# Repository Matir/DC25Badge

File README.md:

## Matir's DEF CON 25 Badge ##

This is an unofficial badge I made for DEF CON 25.  It's a blinding party-style
badge with 48 individually addressable RGB LEDs.  Off an adequate battery (a
medium LiPo) you can run all lights at max brightness, but that is *bright*.

This is intended as a one-time release for others to learn from and/or remix the
firmware.  I don't plan to take pull requests since it will be over and I'll be
on to another project by the release.  :)

### PCB ###

The PCB was designed using Kicad.  Source files are in the `dc25badge/`
directory.

### Compiling Firmware ###

To build the firmware, you'll need 3 things: this git repository, the Atmel
Software Framework (ASF), and an ARM compiler.  On Debian & Ubuntu, you'll want
to install the packages `gcc-arm-none-eabi` and `binutils-arm-none-eabi`.

`setup.sh` in the `src/` directory will get you the latest build of the ASF (at
least, it worked when this was prepared).  Running `make` will build the
firmware image.

To choose which patterns are available by pushing the mode button, edit the
array in `pattern.c`.

### Uploading Firmware ###

To upload a firmware image, you'll need to get into the bootloader.  To do this,
"double tap" the reset button, and the reset LED will stay solid green.  (If it
doesn't, you're not in the bootloader.)

You can then use `bossa` or just run `make upload` from the `src/` directory to
upload the current firmware build.

This is not an official Google product.

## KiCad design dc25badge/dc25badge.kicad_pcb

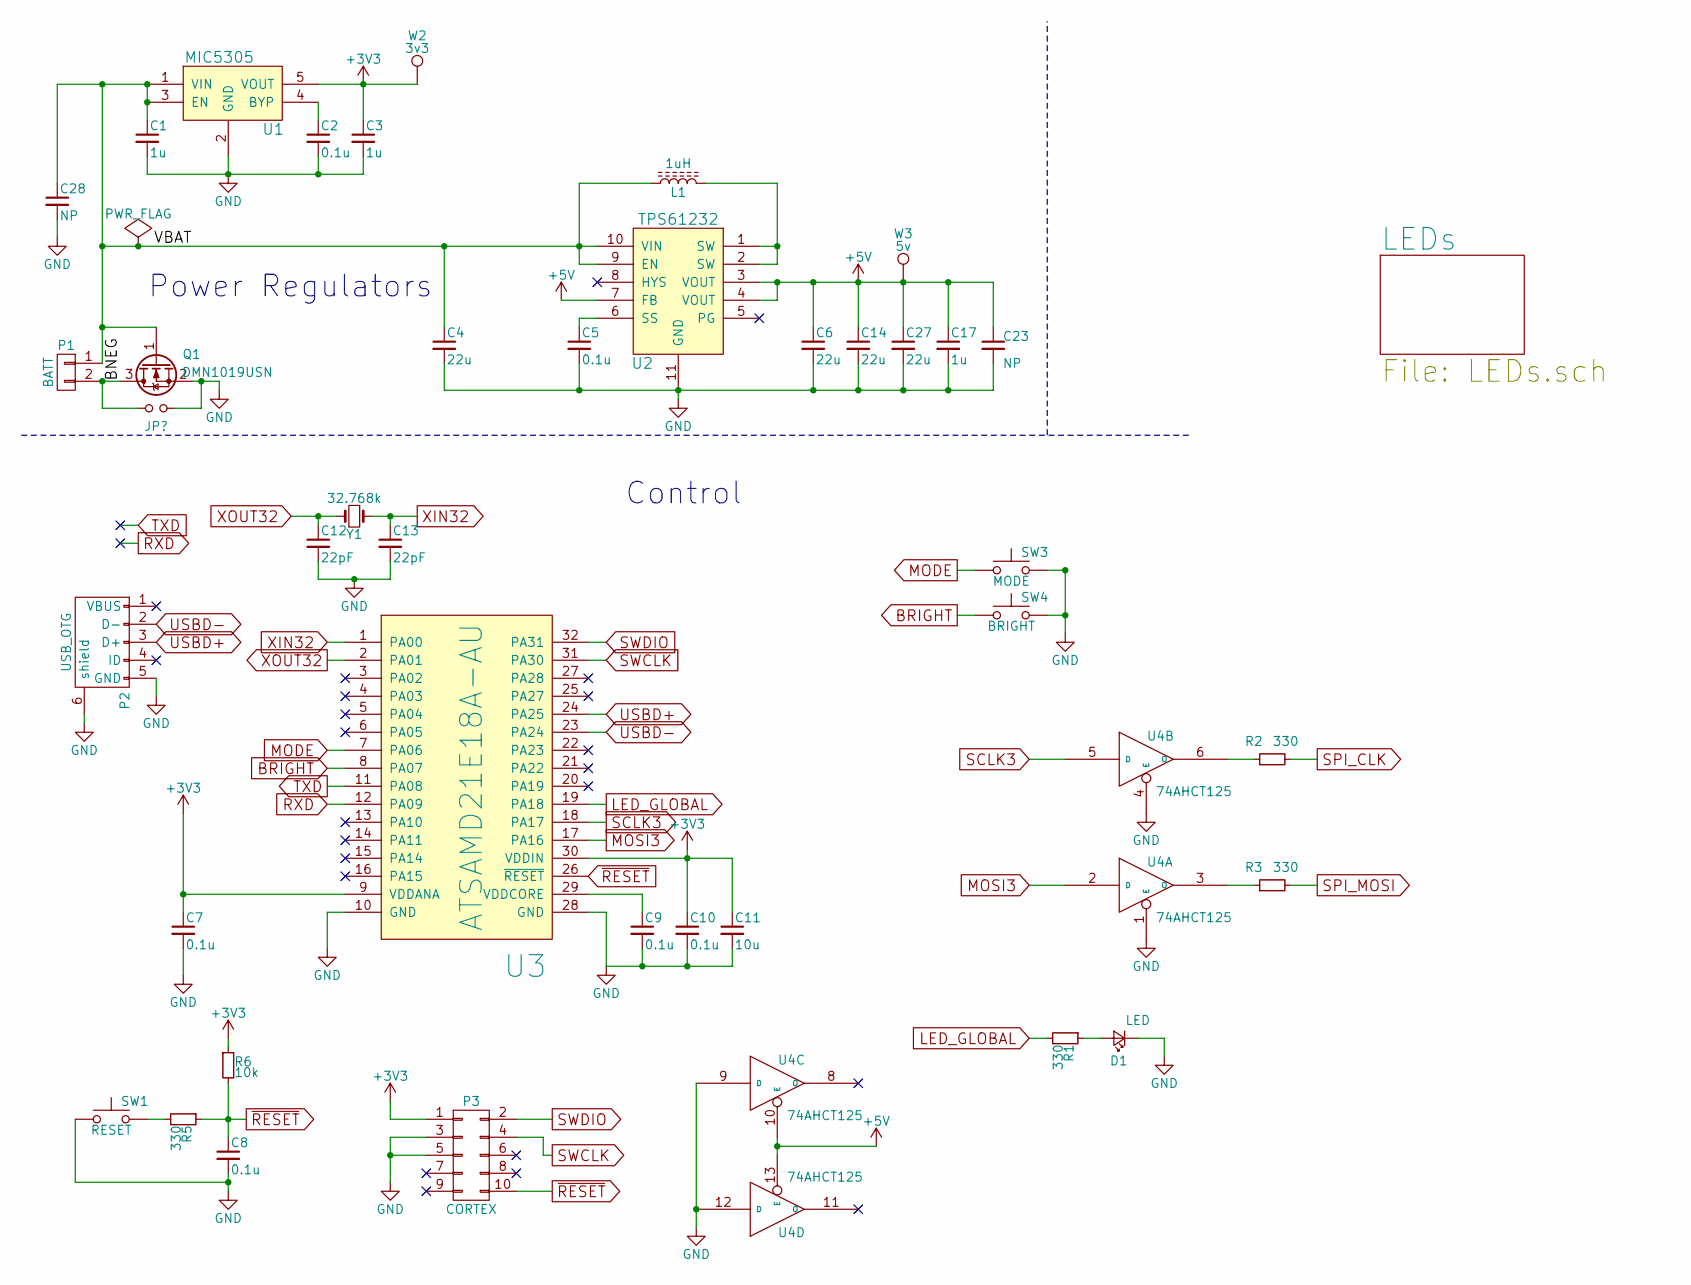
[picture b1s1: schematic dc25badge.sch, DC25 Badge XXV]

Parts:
C1, C3, C17: 1u; C_0805
C2, C5, C7, C8, C9, C10: 0.1u; C_0805
C4, C6, C14, C27: 22u; C_0805
C11: 10u; C_0805
C12, C13: 22pF; C_0603
C23, C28: NP; C_0805
D1: LED; LED_0805
L1: 1uH; Inductor_6.5x6
P1: BATT; JST_PH_S2B-PH-SM4-TB_02x2.00mm_Angled
P2: USB_OTG; Amphenol_10118192
P3: CORTEX; Pin_Header_Straight_2x05_Pitch1.27mm_SMD
Q1: DMN1019USN; SOT-23
R1, R2, R3, R5: 330; R_0805
R6: 10k; R_0805
SW1: RESET; SW_SPST_EVQP0
SW3: MODE; SW_SPST_EVQP0
SW4: BRIGHT; SW_SPST_EVQP0
U1: MIC5305; SOT-23-5
U2: TPS61232; PSON-10P
U3: ATSAMD21E18A-AU; TQFP-32_7x7mm_Pitch0.8mm
U4: 74AHCT125; SOIC-14_N
W2: 3v3; Measurement_Point_Round-SMD-Pad_Big
W3: 5v; Measurement_Point_Round-SMD-Pad_Big
Y1: 32.768k; Crystal_SMD_G8

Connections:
+3V3: C3.1, C7.1, C10.1, C11.1, P3.1, R6.1, U1.5 (VOUT), U3.9 (VDDANA), U3.30 (VDDIN), W2.1
+5V: C6.1, C14.1, C17.1, C23.1, C27.1, U2.3 (VOUT), U2.4 (VOUT), U2.7 (FB), U4.10 (E), U4.13 (E), U4.14 (+5V), W3.1; also elsewhere on the board
/BNEG: P1.2, Q1.3 (D); also elsewhere on the board
/VBAT: C1.1, C4.1, C28.1, L1.1, P1.1, Q1.1 (G), U1.1 (VIN), U1.3 (EN), U2.9 (EN), U2.10 (VIN)
BRIGHT: SW4.1, U3.8 (PA07)
GND: C1.2, C2.2, C3.2, C4.2, C5.2, C6.2, C7.2, C8.2, C9.2, C10.2, C11.2, C12.2, C13.2, C14.2, C17.2, C23.2, C27.2, C28.2, D1.1 (K), P2.5 (GND), P2.6 (shield), P3.3, P3.5, Q1.2 (S), SW1.1, SW3.2, SW4.2, U1.2 (GND), U2.11 (GND), U3.10 (GND), U3.28 (GND), U4.1 (E), U4.4 (E), U4.7 (GND), U4.9 (D), U4.12 (D); also elsewhere on the board
LED_GLOBAL: R1.2, U3.19 (PA18)
MODE: SW3.1, U3.7 (PA06)
MOSI3: U3.17 (PA16), U4.2 (D)
unnamed: C2.1, U1.4 (BYP)
unnamed: C5.1, U2.6 (SS)
unnamed: C9.1, U3.29 (VDDCORE)
unnamed: D1.2 (A), R1.1
unnamed: L1.2, U2.1 (SW), U2.2 (SW)
unnamed: R2.1, U4.6 (O)
unnamed: R3.1, U4.3 (O)
unnamed: R5.2, SW1.2
RXD: U3.12 (PA09)
SCLK3: U3.18 (PA17), U4.5 (D)
SPI_CLK: R2.2; also elsewhere on the board
SPI_MOSI: R3.2; also elsewhere on the board
SWCLK: P3.4, U3.31 (PA30)
SWDIO: P3.2, U3.32 (PA31)
TXD: U3.11 (PA08)
USBD+: P2.3 (D+), U3.24 (PA25)
USBD-: P2.2 (D-), U3.23 (PA24)
XIN32: C13.1, U3.1 (PA00), Y1.1
XOUT32: C12.1, U3.2 (PA01), Y1.2
~RESET: C8.1, P3.10, R5.1, R6.2, U3.26 (~RESET)

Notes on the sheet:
Power Regulators
Control

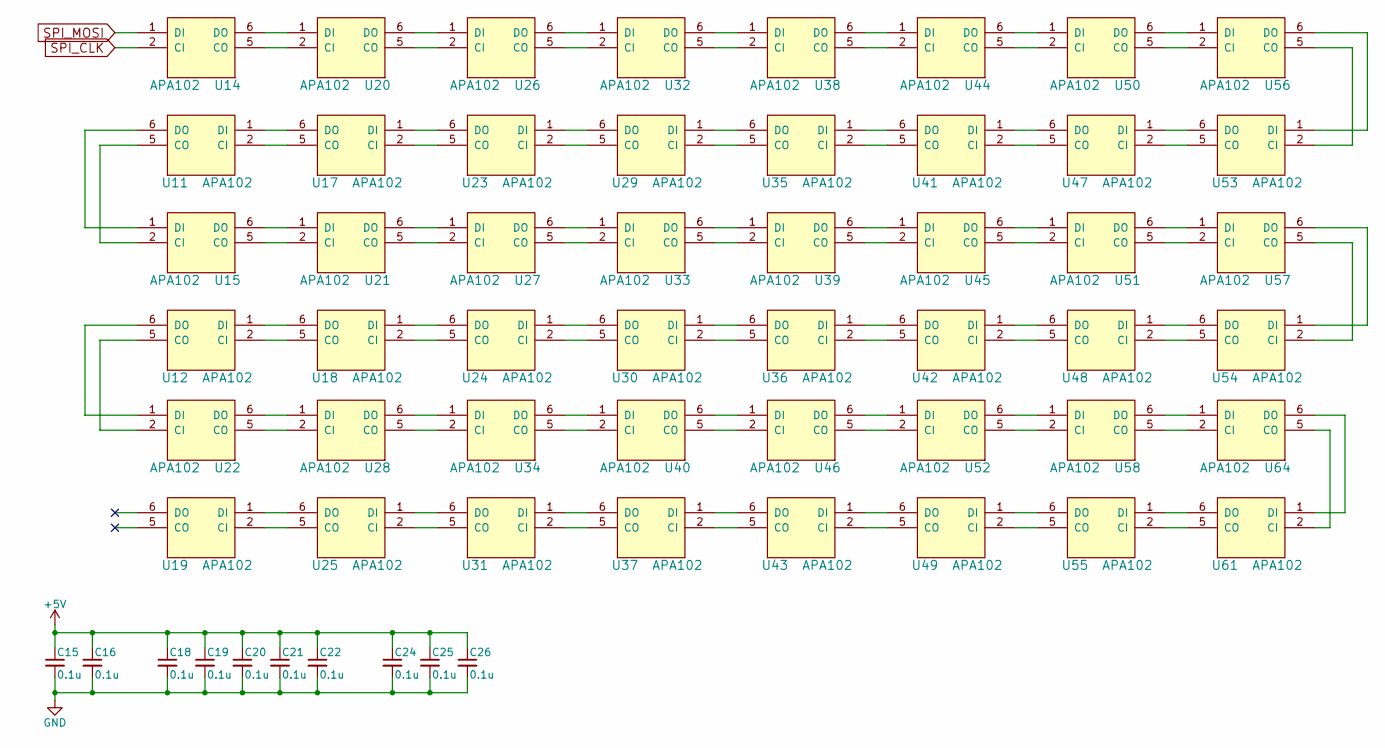
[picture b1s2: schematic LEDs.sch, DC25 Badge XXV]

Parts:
C15, C16, C18, C19, C20, C21, C22, C24, C25, C26: 0.1u; C_0805
U11, U12, U14, U15, U17, U18, U19, U20, U21, U22, U23, U24, U25, U26, U27, U28, U29, U30, U31, U32, U33, U34, U35, U36, U37, U38, U39, U40, U41, U42, U43, U44, U45, U46, U47, U48, U49, U50, U51, U52, U53, U54, U55, U56, U57, U58, U61, U64: APA102

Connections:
+5V: C15.1, C16.1, C18.1, C19.1, C20.1, C21.1, C22.1, C24.1, C25.1, C26.1, U11.4 (+5V), U12.4 (+5V), U14.4 (+5V), U15.4 (+5V), U17.4 (+5V), U18.4 (+5V), U19.4 (+5V), U20.4 (+5V), U21.4 (+5V), U22.4 (+5V), U23.4 (+5V), U24.4 (+5V), U25.4 (+5V), U26.4 (+5V), U27.4 (+5V), U28.4 (+5V), U29.4 (+5V), U30.4 (+5V), U31.4 (+5V), U32.4 (+5V), U33.4 (+5V), U34.4 (+5V), U35.4 (+5V), U36.4 (+5V), U37.4 (+5V), U38.4 (+5V), U39.4 (+5V), U40.4 (+5V), U41.4 (+5V), U42.4 (+5V), U43.4 (+5V), U44.4 (+5V), U45.4 (+5V), U46.4 (+5V), U47.4 (+5V), U48.4 (+5V), U49.4 (+5V), U50.4 (+5V), U51.4 (+5V), U52.4 (+5V), U53.4 (+5V), U54.4 (+5V), U55.4 (+5V), U56.4 (+5V), U57.4 (+5V), U58.4 (+5V), U61.4 (+5V), U64.4 (+5V); also elsewhere on the board
GND: C15.2, C16.2, C18.2, C19.2, C20.2, C21.2, C22.2, C24.2, C25.2, C26.2, U11.3 (GND), U12.3 (GND), U14.3 (GND), U15.3 (GND), U17.3 (GND), U18.3 (GND), U19.3 (GND), U20.3 (GND), U21.3 (GND), U22.3 (GND), U23.3 (GND), U24.3 (GND), U25.3 (GND), U26.3 (GND), U27.3 (GND), U28.3 (GND), U29.3 (GND), U30.3 (GND), U31.3 (GND), U32.3 (GND), U33.3 (GND), U34.3 (GND), U35.3 (GND), U36.3 (GND), U37.3 (GND), U38.3 (GND), U39.3 (GND), U40.3 (GND), U41.3 (GND), U42.3 (GND), U43.3 (GND), U44.3 (GND), U45.3 (GND), U46.3 (GND), U47.3 (GND), U48.3 (GND), U49.3 (GND), U50.3 (GND), U51.3 (GND), U52.3 (GND), U53.3 (GND), U54.3 (GND), U55.3 (GND), U56.3 (GND), U57.3 (GND), U58.3 (GND), U61.3 (GND), U64.3 (GND); also elsewhere on the board
unnamed: U11.1 (DI), U17.6 (DO)
unnamed: U11.2 (CI), U17.5 (CO)
unnamed: U11.5 (CO), U15.2 (CI)
unnamed: U11.6 (DO), U15.1 (DI)
unnamed: U12.1 (DI), U18.6 (DO)
unnamed: U12.2 (CI), U18.5 (CO)
unnamed: U12.5 (CO), U22.2 (CI)
unnamed: U12.6 (DO), U22.1 (DI)
unnamed: U14.5 (CO), U20.2 (CI)
unnamed: U14.6 (DO), U20.1 (DI)
unnamed: U15.5 (CO), U21.2 (CI)
unnamed: U15.6 (DO), U21.1 (DI)
unnamed: U17.1 (DI), U23.6 (DO)
unnamed: U17.2 (CI), U23.5 (CO)
unnamed: U18.1 (DI), U24.6 (DO)
unnamed: U18.2 (CI), U24.5 (CO)
unnamed: U19.1 (DI), U25.6 (DO)
unnamed: U19.2 (CI), U25.5 (CO)
unnamed: U20.5 (CO), U26.2 (CI)
unnamed: U20.6 (DO), U26.1 (DI)
unnamed: U21.5 (CO), U27.2 (CI)
unnamed: U21.6 (DO), U27.1 (DI)
unnamed: U22.5 (CO), U28.2 (CI)
unnamed: U22.6 (DO), U28.1 (DI)
unnamed: U23.1 (DI), U29.6 (DO)
unnamed: U23.2 (CI), U29.5 (CO)
unnamed: U24.1 (DI), U30.6 (DO)
unnamed: U24.2 (CI), U30.5 (CO)
unnamed: U25.1 (DI), U31.6 (DO)
unnamed: U25.2 (CI), U31.5 (CO)
unnamed: U26.5 (CO), U32.2 (CI)
unnamed: U26.6 (DO), U32.1 (DI)
unnamed: U27.5 (CO), U33.2 (CI)
unnamed: U27.6 (DO), U33.1 (DI)
unnamed: U28.5 (CO), U34.2 (CI)
unnamed: U28.6 (DO), U34.1 (DI)
unnamed: U29.1 (DI), U35.6 (DO)
unnamed: U29.2 (CI), U35.5 (CO)
unnamed: U30.1 (DI), U36.6 (DO)
unnamed: U30.2 (CI), U36.5 (CO)
unnamed: U31.1 (DI), U37.6 (DO)
unnamed: U31.2 (CI), U37.5 (CO)
unnamed: U32.5 (CO), U38.2 (CI)
unnamed: U32.6 (DO), U38.1 (DI)
unnamed: U33.5 (CO), U39.2 (CI)
unnamed: U33.6 (DO), U39.1 (DI)
unnamed: U34.5 (CO), U40.2 (CI)
unnamed: U34.6 (DO), U40.1 (DI)
unnamed: U35.1 (DI), U41.6 (DO)
unnamed: U35.2 (CI), U41.5 (CO)
unnamed: U36.1 (DI), U42.6 (DO)
unnamed: U36.2 (CI), U42.5 (CO)
unnamed: U37.1 (DI), U43.6 (DO)
unnamed: U37.2 (CI), U43.5 (CO)
unnamed: U38.5 (CO), U44.2 (CI)
unnamed: U38.6 (DO), U44.1 (DI)
unnamed: U39.5 (CO), U45.2 (CI)
unnamed: U39.6 (DO), U45.1 (DI)
unnamed: U40.5 (CO), U46.2 (CI)
unnamed: U40.6 (DO), U46.1 (DI)
unnamed: U41.1 (DI), U47.6 (DO)
unnamed: U41.2 (CI), U47.5 (CO)
unnamed: U42.1 (DI), U48.6 (DO)
unnamed: U42.2 (CI), U48.5 (CO)
unnamed: U43.1 (DI), U49.6 (DO)
unnamed: U43.2 (CI), U49.5 (CO)
unnamed: U44.5 (CO), U50.2 (CI)
unnamed: U44.6 (DO), U50.1 (DI)
unnamed: U45.5 (CO), U51.2 (CI)
unnamed: U45.6 (DO), U51.1 (DI)
unnamed: U46.5 (CO), U52.2 (CI)
unnamed: U46.6 (DO), U52.1 (DI)
unnamed: U47.1 (DI), U53.6 (DO)
unnamed: U47.2 (CI), U53.5 (CO)
unnamed: U48.1 (DI), U54.6 (DO)
unnamed: U48.2 (CI), U54.5 (CO)
unnamed: U49.1 (DI), U55.6 (DO)
unnamed: U49.2 (CI), U55.5 (CO)
unnamed: U50.5 (CO), U56.2 (CI)
unnamed: U50.6 (DO), U56.1 (DI)
unnamed: U51.5 (CO), U57.2 (CI)
unnamed: U51.6 (DO), U57.1 (DI)
unnamed: U52.5 (CO), U58.2 (CI)
unnamed: U52.6 (DO), U58.1 (DI)
unnamed: U53.1 (DI), U56.6 (DO)
unnamed: U53.2 (CI), U56.5 (CO)
unnamed: U54.1 (DI), U57.6 (DO)
unnamed: U54.2 (CI), U57.5 (CO)
unnamed: U55.1 (DI), U61.6 (DO)
unnamed: U55.2 (CI), U61.5 (CO)
unnamed: U58.5 (CO), U64.2 (CI)
unnamed: U58.6 (DO), U64.1 (DI)
unnamed: U61.1 (DI), U64.6 (DO)
unnamed: U61.2 (CI), U64.5 (CO)
SPI_CLK: U14.2 (CI); also elsewhere on the board
SPI_MOSI: U14.1 (DI); also elsewhere on the board

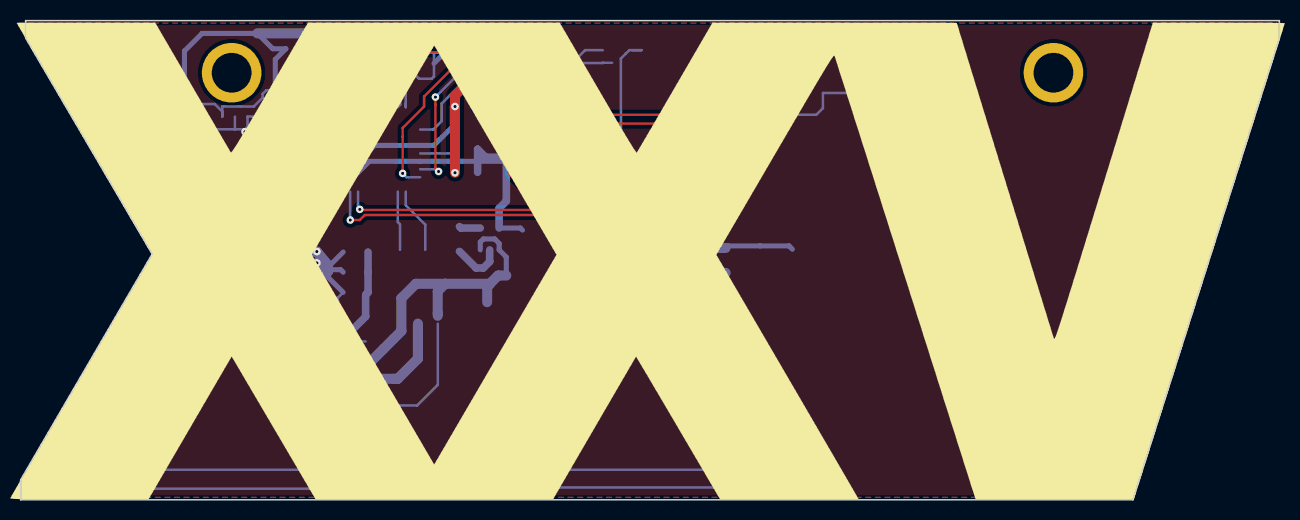
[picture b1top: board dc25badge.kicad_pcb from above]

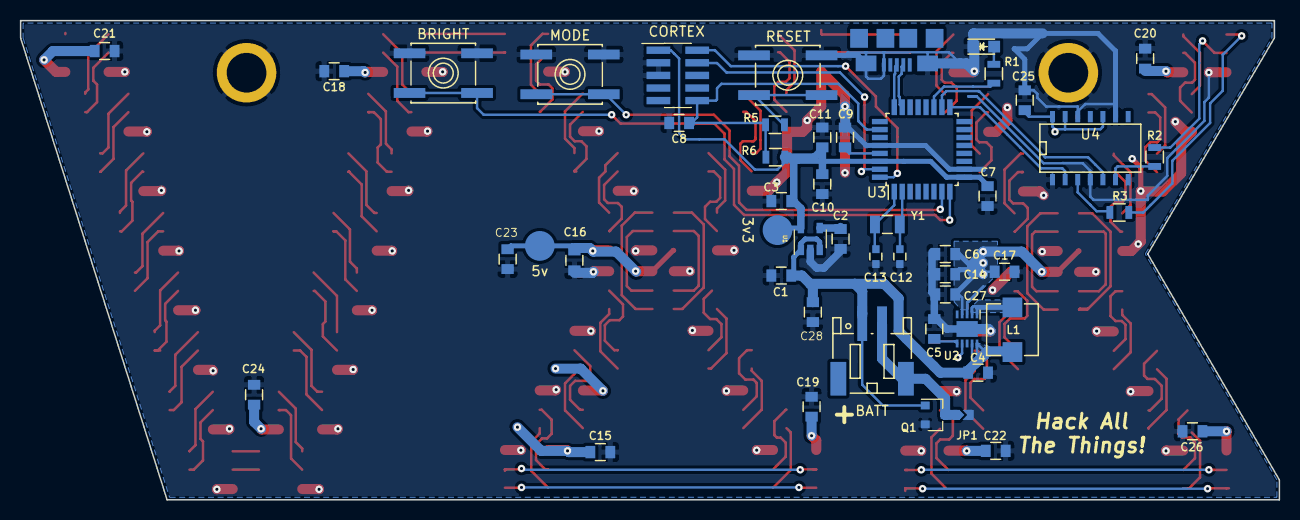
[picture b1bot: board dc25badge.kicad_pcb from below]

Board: 2 copper layers, 126.8 x 48.2 mm, 98 parts (50 on the bottom side), 121 nets.

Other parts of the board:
JP1: Jumper_NO_Small; JP_SOLDER

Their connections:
/BNEG: JP1.1; also elsewhere on the board
GND: JP1.2; also elsewhere on the board

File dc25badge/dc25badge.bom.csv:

Reference, Value, Footprint, Datasheet
"U1","MIC5305","TO_SOT_Packages_SMD:SOT-23-5",""
"P1","BATT","Connectors_JST:JST_PH_S2B-PH-SM4-TB_02x2.00mm_Angled",""
"C2","0.1u","Capacitors_SMD:C_0805",""
"C1","1u","Capacitors_SMD:C_0805",""
"C3","1u","Capacitors_SMD:C_0805",""
"U3","ATSAMD21E18A-AU","Housings_QFP:TQFP-32_7x7mm_Pitch0.8mm",""
"C7","0.1u","Capacitors_SMD:C_0805",""
"C9","0.1u","Capacitors_SMD:C_0805",""
"C10","0.1u","Capacitors_SMD:C_0805",""
"R6","10k","Resistors_SMD:R_0805",""
"C11","10u","Capacitors_SMD:C_0805",""
"C8","0.1u","Capacitors_SMD:C_0805",""
"R5","330","Resistors_SMD:R_0805",""
"SW1","RESET","Buttons_Switches_SMD:SW_SPST_EVQP0",""
"P3","CORTEX","Pin_Headers2:Pin_Header_Straight_2x05_Pitch1.27mm_SMD",""
"P2","USB_OTG","Badge_Parts:Amphenol_10118192",""
"U4","74AHCT125","SMD_Packages:SOIC-14_N",""
"W2","3v3","Measurement_Points:Measurement_Point_Round-SMD-Pad_Big",""
"W3","5v","Measurement_Points:Measurement_Point_Round-SMD-Pad_Big",""
"Y1","32.768k","Crystals:Crystal_SMD_G8",""
"C13","22pF","Capacitors_SMD:C_0603",""
"C12","22pF","Capacitors_SMD:C_0603",""
"SW3","MODE","Buttons_Switches_SMD:SW_SPST_EVQP0",""
"SW4","BRIGHT","Buttons_Switches_SMD:SW_SPST_EVQP0",""
"U2","TPS61232","Badge_Parts:PSON-10P",""
"C5","0.1u","Capacitors_SMD:C_0805",""
"L1","1uH","Badge_Parts:Inductor_6.5x6",""
"C4","22u","Capacitors_SMD:C_0805",""
"C6","22u","Capacitors_SMD:C_0805",""
"C14","22u","Capacitors_SMD:C_0805",""
"C27","22u","Capacitors_SMD:C_0805",""
"R1","330","Resistors_SMD:R_0805",""
"D1","LED","LEDs:LED_0805",""
"Q1","DMN1019USN","TO_SOT_Packages_SMD:SOT-23",""
"C17","1u","Capacitors_SMD:C_0805",""
"R2","330","Resistors_SMD:R_0805",""
"R3","330","Resistors_SMD:R_0805",""
"U38","APA102","Badge_Parts:APA102",""
"U44","APA102","Badge_Parts:APA102",""
"U50","APA102","Badge_Parts:APA102",""
"U56","APA102","Badge_Parts:APA102",""
"U14","APA102","Badge_Parts:APA102",""
"U20","APA102","Badge_Parts:APA102",""
"U26","APA102","Badge_Parts:APA102",""
"U32","APA102","Badge_Parts:APA102",""
"U29","APA102","Badge_Parts:APA102",""
"U23","APA102","Badge_Parts:APA102",""
"U17","APA102","Badge_Parts:APA102",""
"U11","APA102","Badge_Parts:APA102",""
"U53","APA102","Badge_Parts:APA102",""
"U47","APA102","Badge_Parts:APA102",""
"U41","APA102","Badge_Parts:APA102",""
"U35","APA102","Badge_Parts:APA102",""
"U39","APA102","Badge_Parts:APA102",""
"U45","APA102","Badge_Parts:APA102",""
"U51","APA102","Badge_Parts:APA102",""
"U57","APA102","Badge_Parts:APA102",""
"U15","APA102","Badge_Parts:APA102",""
"U21","APA102","Badge_Parts:APA102",""
"U27","APA102","Badge_Parts:APA102",""
"U33","APA102","Badge_Parts:APA102",""
"U30","APA102","Badge_Parts:APA102",""
"U24","APA102","Badge_Parts:APA102",""
"U18","APA102","Badge_Parts:APA102",""
"U12","APA102","Badge_Parts:APA102",""
"U54","APA102","Badge_Parts:APA102",""
"U48","APA102","Badge_Parts:APA102",""
"U42","APA102","Badge_Parts:APA102",""
"U36","APA102","Badge_Parts:APA102",""
"U40","APA102","Badge_Parts:APA102",""
"U46","APA102","Badge_Parts:APA102",""
"U52","APA102","Badge_Parts:APA102",""
"U58","APA102","Badge_Parts:APA102",""
"U64","APA102","Badge_Parts:APA102",""
"U22","APA102","Badge_Parts:APA102",""
"U28","APA102","Badge_Parts:APA102",""
"U34","APA102","Badge_Parts:APA102",""
"U31","APA102","Badge_Parts:APA102",""
"U25","APA102","Badge_Parts:APA102",""
"U19","APA102","Badge_Parts:APA102",""
"U61","APA102","Badge_Parts:APA102",""
"U55","APA102","Badge_Parts:APA102",""
"U49","APA102","Badge_Parts:APA102",""
"U43","APA102","Badge_Parts:APA102",""
"U37","APA102","Badge_Parts:APA102",""
"C15","0.1u","Capacitors_SMD:C_0805",""
"C16","0.1u","Capacitors_SMD:C_0805",""
"C18","0.1u","Capacitors_SMD:C_0805",""
"C19","0.1u","Capacitors_SMD:C_0805",""
"C20","0.1u","Capacitors_SMD:C_0805",""
"C21","0.1u","Capacitors_SMD:C_0805",""
"C22","0.1u","Capacitors_SMD:C_0805",""
"C24","0.1u","Capacitors_SMD:C_0805",""
"C25","0.1u","Capacitors_SMD:C_0805",""
"C26","0.1u","Capacitors_SMD:C_0805",""

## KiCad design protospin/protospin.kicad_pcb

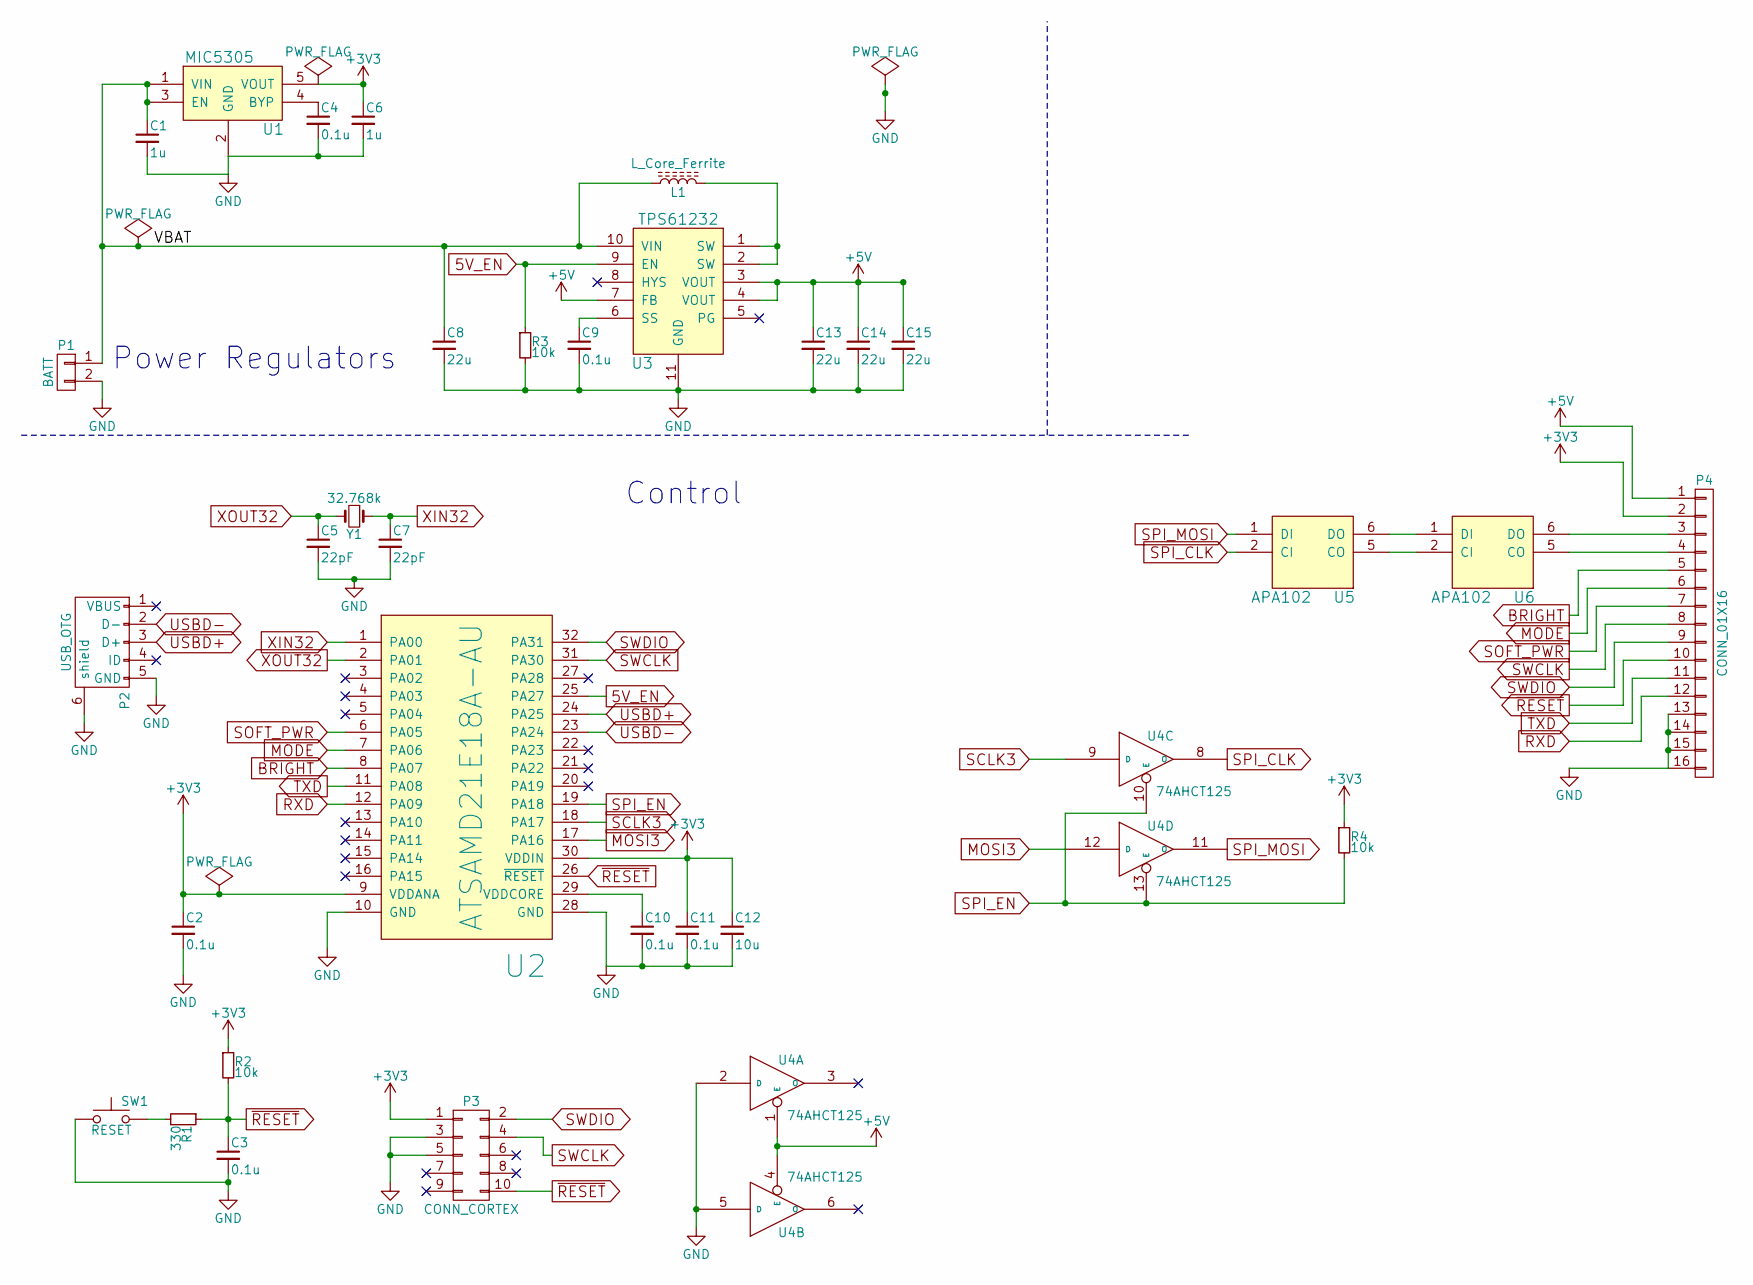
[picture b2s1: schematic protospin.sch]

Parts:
C1, C6: 1u; C_0805_HandSoldering
C2, C3, C4, C9, C10, C11: 0.1u; C_0805_HandSoldering
C5, C7: 22pF; C_0805_HandSoldering
C8, C13, C14, C15: 22u; C_0805_HandSoldering
C12: 10u; C_0805_HandSoldering
L1: L_Core_Ferrite; Inductor_6.5x6
P1: BATT; JST_PH_S2B-PH-SM4-TB_02x2.00mm_Angled
P2: USB_OTG; Amphenol_10118192
P3: CONN_CORTEX; Pin_Header_Straight_2x05_Pitch1.27mm_SMD
P4: CONN_01X16; Pin_Header_Straight_1x16_Pitch2.54mm_SMD_Pin1Right
R1: 330; R_0805_HandSoldering
R2, R3, R4: 10k; R_0805_HandSoldering
SW1: RESET; SW_SPST_EVQP0
U1: MIC5305; SOT-23-5
U2: ATSAMD21E18A-AU; TQFP-32_7x7mm_Pitch0.8mm
U3: TPS61232; PSON-10P
U4: 74AHCT125; SOIC-14_N
U5, U6: APA102
Y1: 32.768k; Crystal_SMD_G8

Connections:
5V_EN: R3.1, U2.25 (PA27), U3.9 (EN)
+3V3: C2.1, C6.1, C11.1, C12.1, P3.1, P4.2, R2.1, R4.1, U1.5 (VOUT), U2.9 (VDDANA), U2.30 (VDDIN)
+5V: C13.1, C14.1, C15.1, P4.1, U3.3 (VOUT), U3.4 (VOUT), U3.7 (FB), U4.1 (E), U4.4 (E), U4.14 (+5V), U5.4 (+5V), U6.4 (+5V)
/VBAT: C1.1, C8.1, L1.1, P1.1, U1.1 (VIN), U1.3 (EN), U3.10 (VIN)
BRIGHT: P4.5, U2.8 (PA07)
GND: C1.2, C2.2, C3.2, C4.2, C5.2, C6.2, C7.2, C8.2, C9.2, C10.2, C11.2, C12.2, C13.2, C14.2, C15.2, P1.2, P2.5 (GND), P2.6 (shield), P3.3, P3.5, P4.13, P4.14, P4.15, P4.16, R3.2, SW1.1, U1.2 (GND), U2.10 (GND), U2.28 (GND), U3.11 (GND), U4.2 (D), U4.5 (D), U4.7 (GND), U5.3 (GND), U6.3 (GND)
MODE: P4.6, U2.7 (PA06)
MOSI3: U2.17 (PA16), U4.12 (D)
unnamed: C4.1, U1.4 (BYP)
unnamed: C9.1, U3.6 (SS)
unnamed: C10.1, U2.29 (VDDCORE)
unnamed: L1.2, U3.1 (SW), U3.2 (SW)
unnamed: P4.3, U6.6 (DO)
unnamed: P4.4, U6.5 (CO)
unnamed: R1.2, SW1.2
unnamed: U5.5 (CO), U6.2 (CI)
unnamed: U5.6 (DO), U6.1 (DI)
RXD: P4.12, U2.12 (PA09)
SCLK3: U2.18 (PA17), U4.9 (D)
SOFT_PWR: P4.7, U2.6 (PA05)
SPI_CLK: U4.8 (O), U5.2 (CI)
SPI_EN: R4.2, U2.19 (PA18), U4.10 (E), U4.13 (E)
SPI_MOSI: U4.11 (O), U5.1 (DI)
SWCLK: P3.4, P4.8, U2.31 (PA30)
SWDIO: P3.2, P4.9, U2.32 (PA31)
TXD: P4.11, U2.11 (PA08)
USBD+: P2.3 (D+), U2.24 (PA25)
USBD-: P2.2 (D-), U2.23 (PA24)
XIN32: C7.1, U2.1 (PA00), Y1.1
XOUT32: C5.1, U2.2 (PA01), Y1.2
~RESET: C3.1, P3.10, P4.10, R1.1, R2.2, U2.26 (~RESET)

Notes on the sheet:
Power Regulators
Control

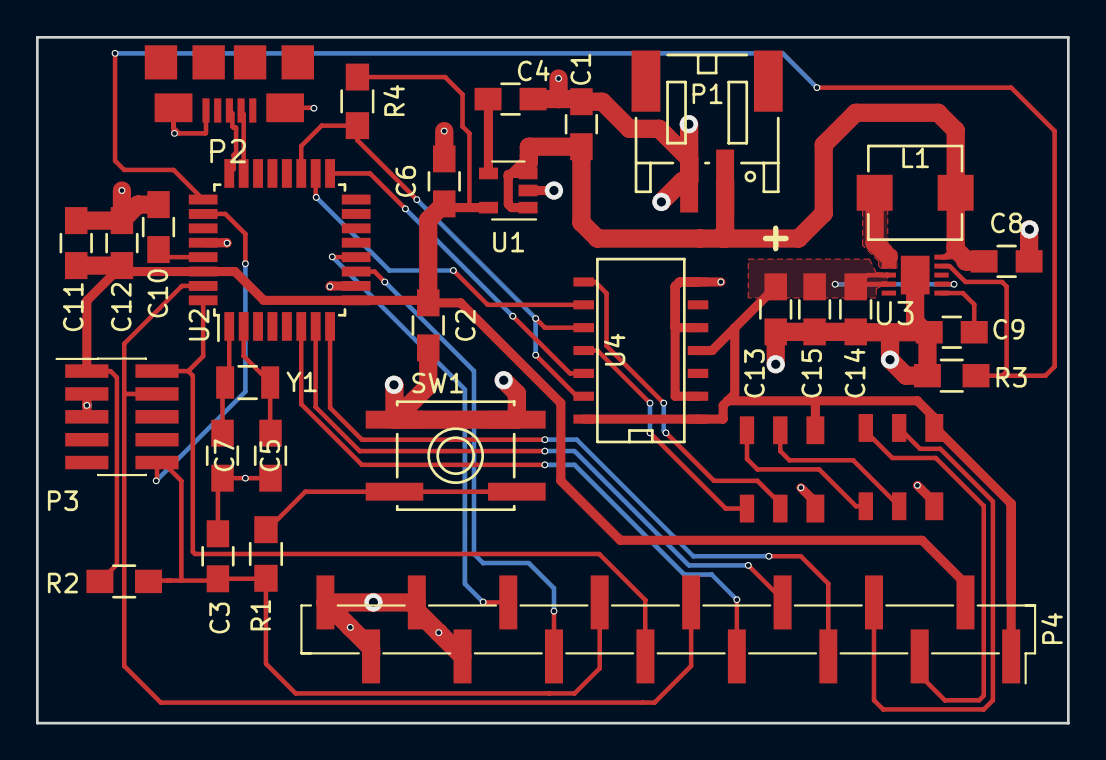
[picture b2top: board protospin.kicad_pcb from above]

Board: 2 copper layers, 57.3 x 38.1 mm, 32 parts (0 on the bottom side), 31 nets.

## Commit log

2017-05-28 First pass at schematic.
2017-05-28 First letter routed.
2017-05-28 Layout all LEDs.
2017-05-29 Routed 1 letter.
2017-05-29 More routing.
2017-05-29 More more routing.
2017-05-29 Route all letters.
2017-05-29 remove old PS.
2017-05-29 schematic for new PS.
2017-05-29 add PS to board.
2017-05-29 Before routing back.
2017-05-29 Full routing.
2017-05-29 Gerbers.
2017-05-29 PCB roll 1.
2017-05-29 Build a small prototype board.
2017-05-29 Fix battery error.
2017-05-30 Switch to 0603 caps on oscillator.
2017-05-30 Rev A protospin.
2017-05-30 Fixup trace clearances.
2017-05-30 Move to 8mil mins.
2017-05-30 Readd cuts.
2017-05-30 Add dimensions.
2017-05-30 Reduce solder mask clearance.
2017-05-31 Add "Designed by @Matir" badge.
2017-05-31 Move to 12mil vias.
2017-05-31 Schematic changes for 48 LED version.
2017-05-31 New board outline, graphics, and LED positions.
2017-06-01 48 LED rebuild.
2017-06-01 48 LED build passes DRC.
2017-06-01 Remove NPTH.
2017-06-01 Silkscreen fixes.
2017-06-01 Update gerbers.
2017-06-01 Adjust soldermask pullback.
2017-06-01 Update notes.
2017-06-01 Switch to a 48-LED compact design.
    Squashed commit of the following:
    commit 6f3d96a4927b58100b9ba94752feefb272124e74
    Author: David Tomaschik <david@systemoverlord.com>
    Date: Thu Jun 1 00:38:57 2017 -0700
    Update notes.
    commit 8834e21676bcc6d408b77b676d72b46c0c38b607
2017-06-01 Update artwork.
2017-06-02 Initial framework.
2017-06-03 Bare minimum to compile!
2017-06-03 Should be a USB CDC device now.
2017-06-03 Add bootloader. I hope.
2017-06-03 Fix bossa uploads by building from source.
2017-06-03 Actually link as thumb too.
2017-06-03 Basic I/O.
2017-06-03 Non-blocking usb-stdio.
2017-06-04 SPI looks right on logic analyzer.
2017-06-04 Red LEDs work.
2017-06-04 Pattern framework start.
2017-06-04 Switch to async SPI.
2017-06-04 Remove use of CS line.
2017-06-04 Add some noise isolation around SPI lines.
2017-06-04 Add indicator LED.
2017-06-05 Working timer setup.
2017-06-05 PCB with LED.
2017-06-05 Fix some brightness bugs.
2017-06-05 Debounce code.
2017-06-07 EESchema update.
2017-06-07 Footprint fixes.
2017-06-07 Protospin stuff.
2017-06-07 Fix edges.
2017-06-09 Add reverse polarity MOSFET.
2017-06-09 Relocate trace.
2017-06-09 Different PINMUX.
2017-06-09 Migrate schematic/PCB changes.
2017-06-09 Debounce handler fixed.
2017-06-09 Button handlers.
2017-06-09 Add proper button handling support.
    Squashed commit of the following:
    commit b09c200419337edb0ed3439eb5f00ea40777bae3
    Author: David Tomaschik <david@systemoverlord.com>
    Date: Thu Jun 8 19:01:07 2017 -0700
    Button handlers.
    commit 2d1f87d350685d3ec55d109bd5e74c913b28586c
2017-06-09 Some dumb demo patterns.
2017-06-09 Config refactor.
2017-06-09 Update source.
2017-06-09 More cap for noise.
2017-06-09 Generate table of constants.
2017-06-10 Add option for anti-ringing resistors.
2017-06-10 BOM bump.
2017-06-10 Update board.
2017-06-10 Update basic patterns.
2017-06-10 Pattern updates.
2017-06-10 This does not work because of asyync interrupts.
2017-06-10 Do not do all the work in interrupt handlers.
2017-06-11 Code now flows correctly.
2017-06-11 Clean up debuggers.
2017-06-11 Smooth at 30fps.
2017-06-11 Use 48MHz DPLL for main clock instead of 8MHz RC oscillator.
2017-06-24 Bootloader fixes.
2017-06-24 Pattern and clocking updates.
2017-06-24 Move components to not be in the way.
2017-06-24 Add jumper to bypass fet.
2017-06-24 Fix jumper footprint.
2017-06-24 No drill map.
2017-06-25 Brightness work.
2017-06-25 Add more patterns.
2017-06-25 Add blinding mode.
2017-06-25 DEBUG options.
2017-06-29 Use protel file extensions.
2017-07-08 Green chase.
2017-07-08 Shutdown after burnin.
2017-07-09 Change bootloader LED.
2017-07-10 Remove outdated notes.
2017-07-10 Add license, move third_party code.
2017-07-10 Add Apache2 headers.
2017-07-11 Remove datasheets.
2017-07-14 Add README, fix headers.
2017-07-23 Fix jumper.
2017-08-01 Pictures of the badge.
2017-08-01 Add PDF of schematic.
2017-08-01 Update BOM.
2017-08-03 Better README.
2017-11-21 Remove template duplication in gentable.py
